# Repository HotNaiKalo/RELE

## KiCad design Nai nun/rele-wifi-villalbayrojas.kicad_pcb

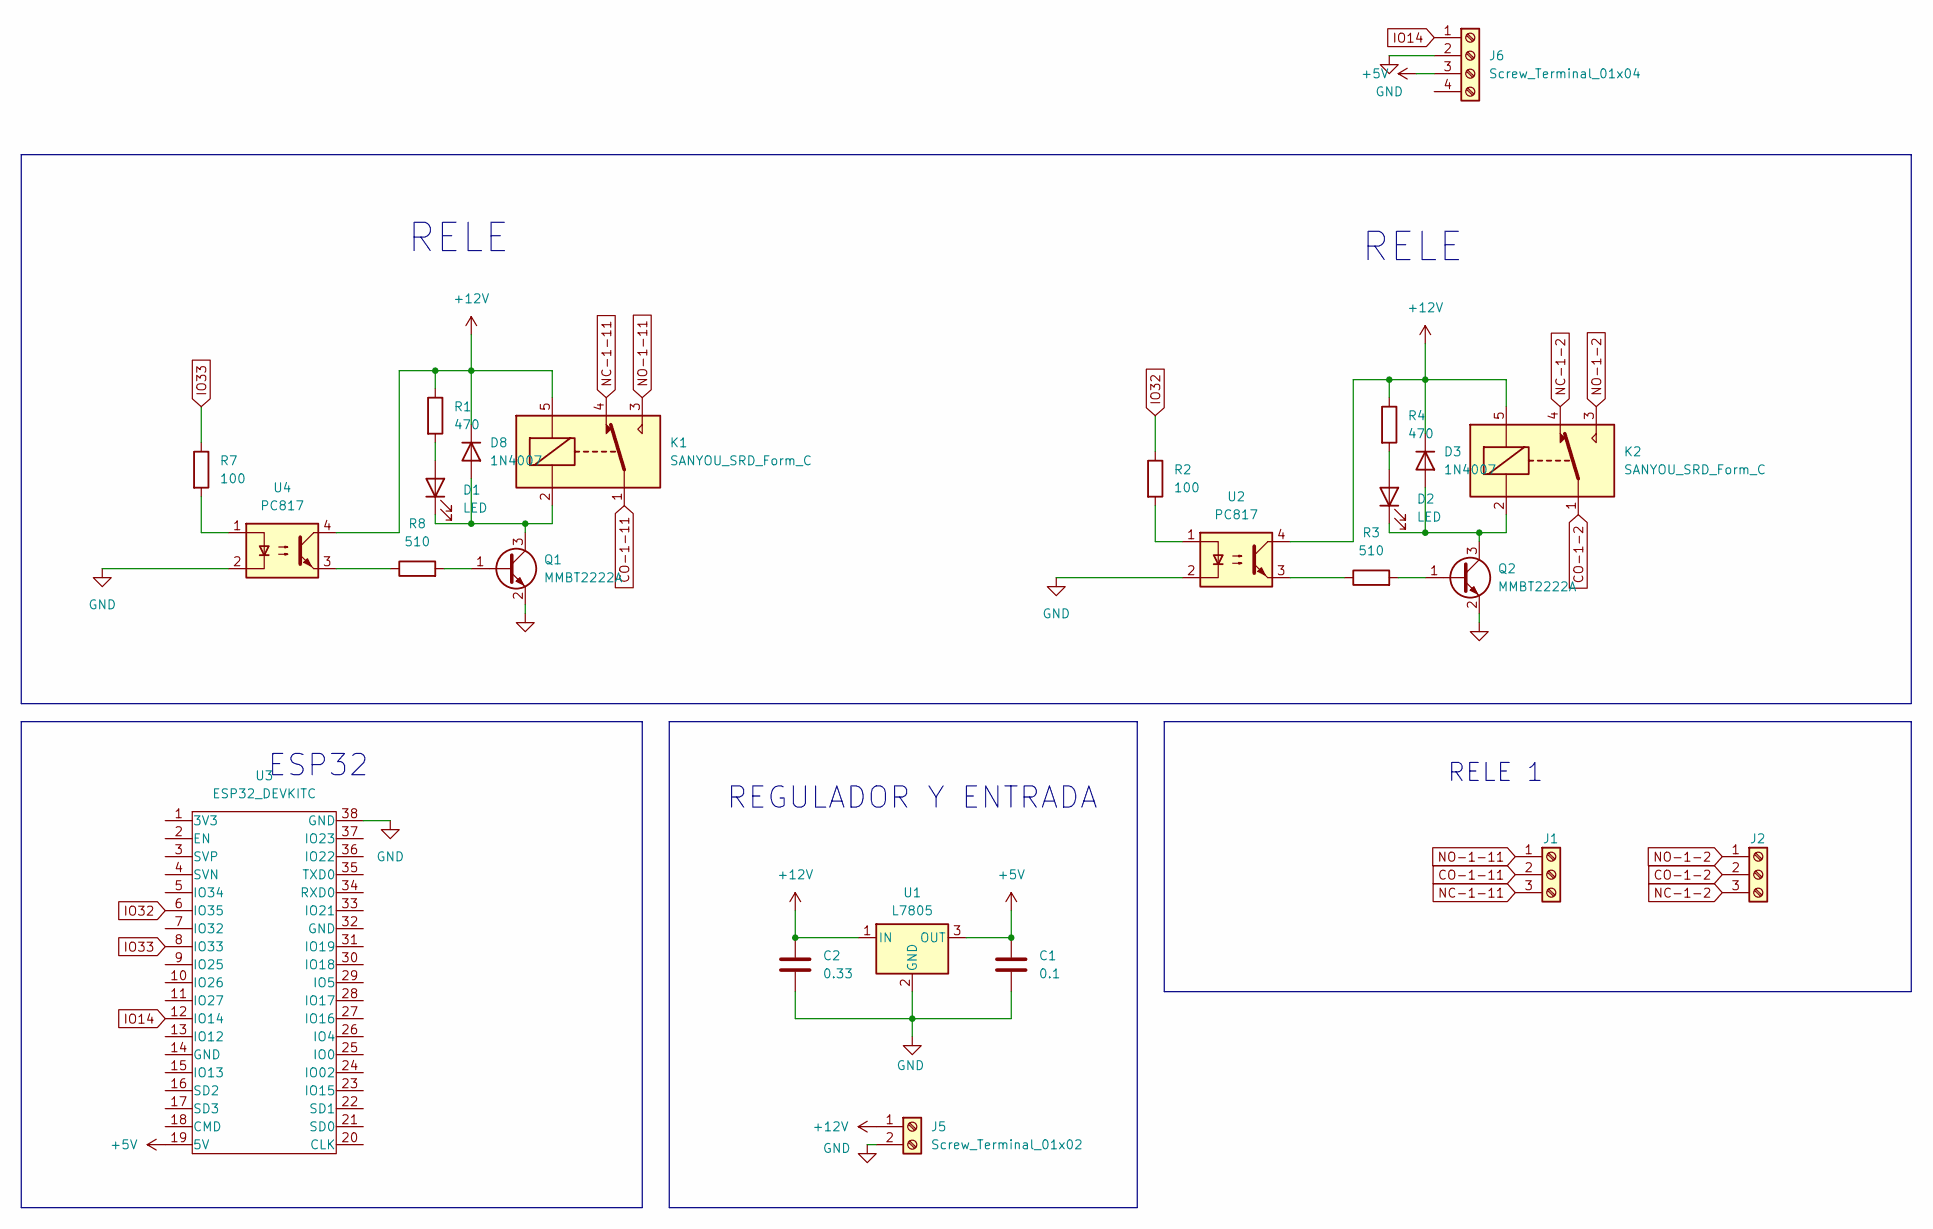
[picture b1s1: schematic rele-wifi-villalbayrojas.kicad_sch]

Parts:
C1: 0.1; C_0805_2012Metric
C2: 0.33; C_0805_2012Metric
D1, D2: LED; LED_0805_2012Metric
D3, D8: 1N4007; D_DO-41_SOD81_P10.16mm_Horizontal
J1, J2: Relay1; TerminalBlock_MaiXu_MX126-5.0-03P_1x03_P5.00mm
J5: Screw_Terminal_01x02; TerminalBlock_MaiXu_MX126-5.0-02P_1x02_P5.00mm
J6: Screw_Terminal_01x04; TerminalBlock_MaiXu_MX126-5.0-04P_1x04_P5.00mm
K1, K2: SANYOU_SRD_Form_C; Relay_SPDT_SANYOU_SRD_Series_Form_C
Q1, Q2: MMBT2222A; SOT-23
R1, R4: 470; R_0805_2012Metric
R2, R7: 100; R_0805_2012Metric
R3, R8: 510; R_0805_2012Metric
U1: L7805; TO-220-3_Vertical
U2, U4: PC817; DIP-4_W7.62mm
U3: ESP32_DEVKITC

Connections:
+5V: C1.1, J6.3, U1.3 (OUT), U3.19 (5V)
+12V: C2.1, D3.1 (K), D8.1 (K), J5.1, K1.5, K2.5, R1.1, R4.1, U1.1 (IN), U2.4, U4.4
CO-1-2: J2.2, K2.1
CO-1-11: J1.2, K1.1
GND: C1.2, C2.2, J5.2, J6.2, Q1.2 (E), Q2.2 (E), U1.2 (GND), U2.2, U3.38 (GND), U4.2
IO14: J6.1, U3.12 (IO14)
IO32: R2.1, U3.6 (IO35)
IO33: R7.1, U3.8 (IO33)
NC-1-2: J2.3, K2.4
NC-1-11: J1.3, K1.4
NO-1-2: J2.1, K2.3
NO-1-11: J1.1, K1.3
unnamed: D1.2 (A), R1.2
unnamed: D1.1 (K), D8.2 (A), K1.2, Q1.3 (C)
unnamed: D2.2 (A), R4.2
unnamed: D2.1 (K), D3.2 (A), K2.2, Q2.3 (C)
unnamed: Q1.1 (B), R8.2
unnamed: Q2.1 (B), R3.2
unnamed: R2.2, U2.1
unnamed: R3.1, U2.3
unnamed: R7.2, U4.1
unnamed: R8.1, U4.3

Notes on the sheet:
RELE
ESP32
RELE 1
REGULADOR Y ENTRADA

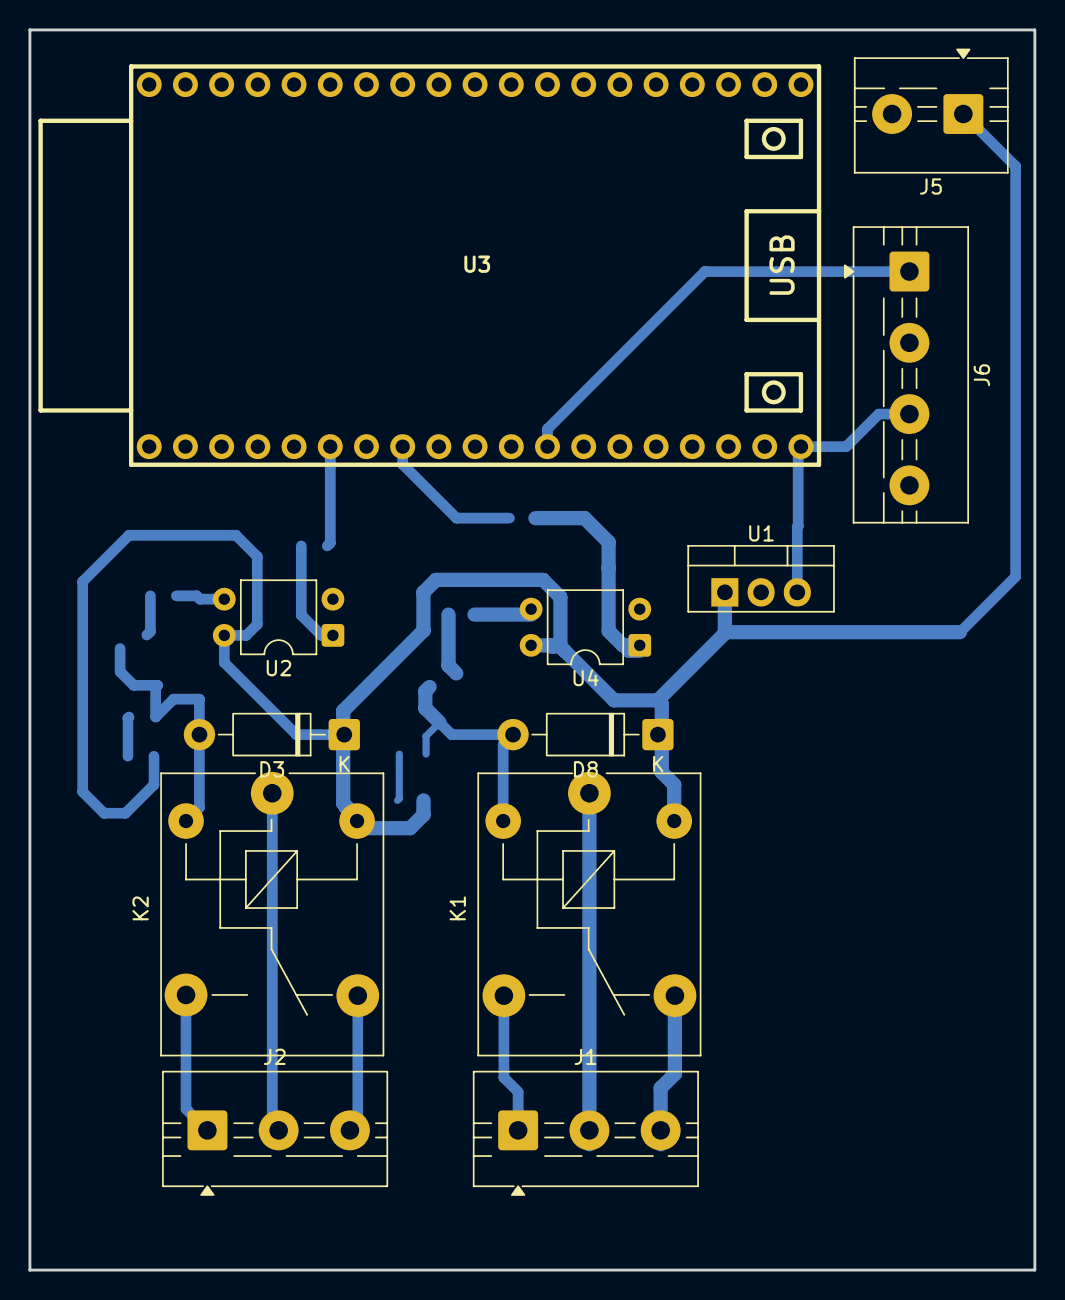
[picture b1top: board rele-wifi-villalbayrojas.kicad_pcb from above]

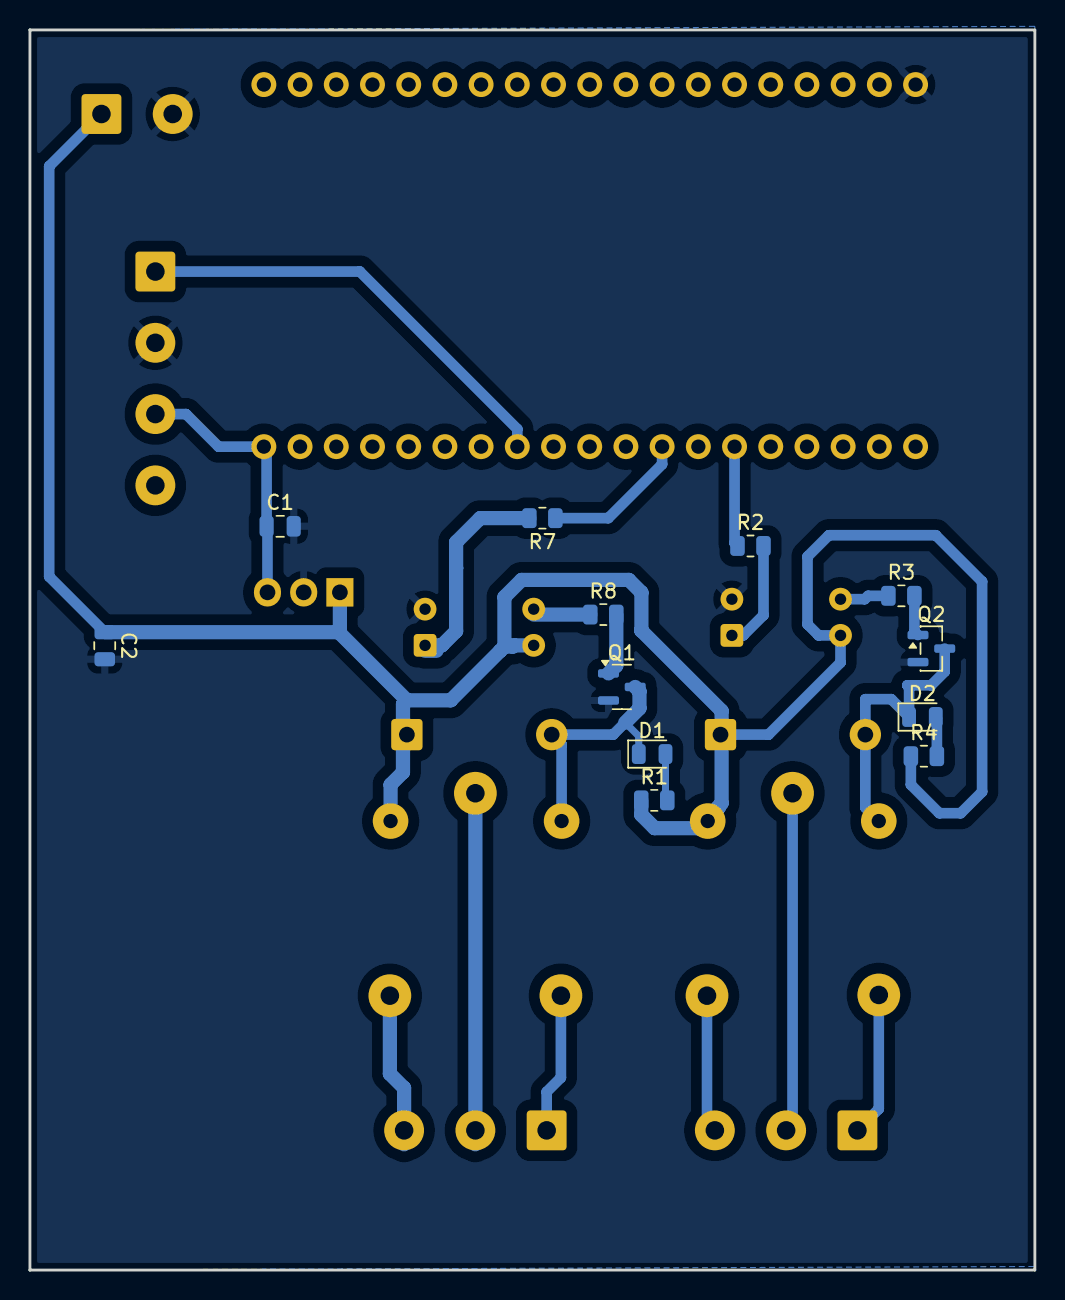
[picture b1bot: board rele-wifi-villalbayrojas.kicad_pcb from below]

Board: 2 copper layers, 70.5 x 87.0 mm, 24 parts (12 on the bottom side), 22 nets.

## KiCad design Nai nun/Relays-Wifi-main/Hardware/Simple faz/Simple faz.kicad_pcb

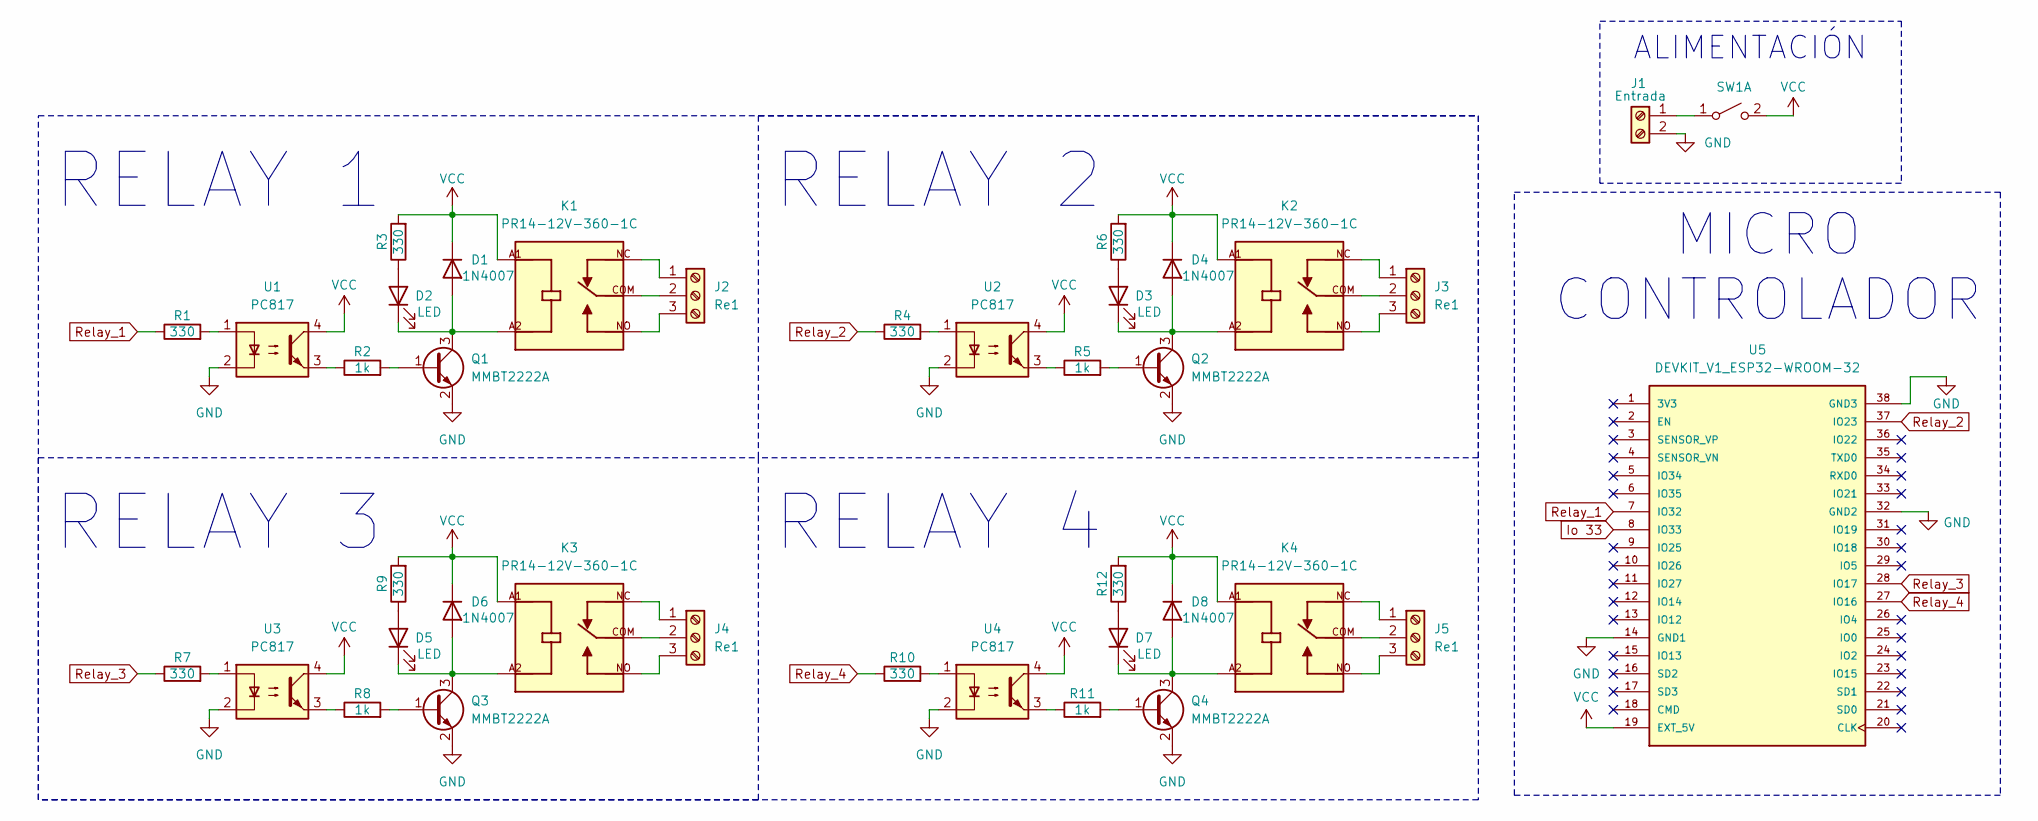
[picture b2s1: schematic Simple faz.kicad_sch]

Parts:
D1, D4, D6, D8: 1N4007; D_SMA
D2, D3, D5, D7: LED; LED_0805_2012Metric
J1: Entrada; TerminalBlock_4Ucon_1x02_P3.50mm_Vertical
J2, J3, J4, J5: Re1; TerminalBlock_4Ucon_1x03_P3.50mm_Vertical
K1, K2, K3, K4: PR14-12V-360-1C; RELAY_PR14-12V-360-1C; PARTREV 1.0
Q1, Q2, Q3, Q4: MMBT2222A; SOT-23
R1, R3, R4, R6, R7, R9, R10, R12: 330; R_0805_2012Metric_Pad1.20x1.40mm_HandSolder
R2, R5, R8, R11: 1k; R_0805_2012Metric_Pad1.20x1.40mm_HandSolder
SW1: PinSocket_1x02_P2.54mm_Vertical
U1, U2, U3, U4: PC817; SMDIP-4_W7.62mm
U5: DEVKIT_V1_ESP32-WROOM-32; ESP32S; PARTREV N/A

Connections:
GND: J1.2, Q1.2 (E), Q2.2 (E), Q3.2 (E), Q4.2 (E), U1.2, U2.2, U3.2, U4.2, U5.14 (GND1), U5.32 (GND2), U5.38 (GND3)
Io 33: U5.8 (IO33)
unnamed: D1.2 (A), D2.1 (K), K1.A2, Q1.3 (C)
unnamed: D2.2 (A), R3.1
unnamed: D3.2 (A), R6.1
unnamed: D3.1 (K), D4.2 (A), K2.A2, Q2.3 (C)
unnamed: D5.2 (A), R9.1
unnamed: D5.1 (K), D6.2 (A), K3.A2, Q3.3 (C)
unnamed: D7.2 (A), R12.1
unnamed: D7.1 (K), D8.2 (A), K4.A2, Q4.3 (C)
unnamed: J1.1, SW1.1 (A)
unnamed: J2.1, K1.NC
unnamed: J2.2, K1.COM
unnamed: J2.3, K1.NO
unnamed: J3.1, K2.NC
unnamed: J3.2, K2.COM
unnamed: J3.3, K2.NO
unnamed: J4.1, K3.NC
unnamed: J4.2, K3.COM
unnamed: J4.3, K3.NO
unnamed: J5.1, K4.NC
unnamed: J5.2, K4.COM
unnamed: J5.3, K4.NO
unnamed: Q1.1 (B), R2.2
unnamed: Q2.1 (B), R5.2
unnamed: Q3.1 (B), R8.2
unnamed: Q4.1 (B), R11.2
unnamed: R1.2, U1.1
unnamed: R2.1, U1.3
unnamed: R4.2, U2.1
unnamed: R5.1, U2.3
unnamed: R7.2, U3.1
unnamed: R8.1, U3.3
unnamed: R10.2, U4.1
unnamed: R11.1, U4.3
Relay_1: R1.1, U5.7 (IO32)
Relay_2: R4.1, U5.37 (IO23)
Relay_3: R7.1, U5.28 (IO17)
Relay_4: R10.1, U5.27 (IO16)
VCC: D1.1 (K), D4.1 (K), D6.1 (K), D8.1 (K), K1.A1, K2.A1, K3.A1, K4.A1, R3.2, R6.2, R9.2, R12.2, SW1.2 (B), U1.4, U2.4, U3.4, U4.4, U5.19 (EXT_5V)

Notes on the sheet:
ALIMENTACIÓN
RELAY 4
RELAY 3
MICRO CONTROLADOR
RELAY 2
RELAY 1

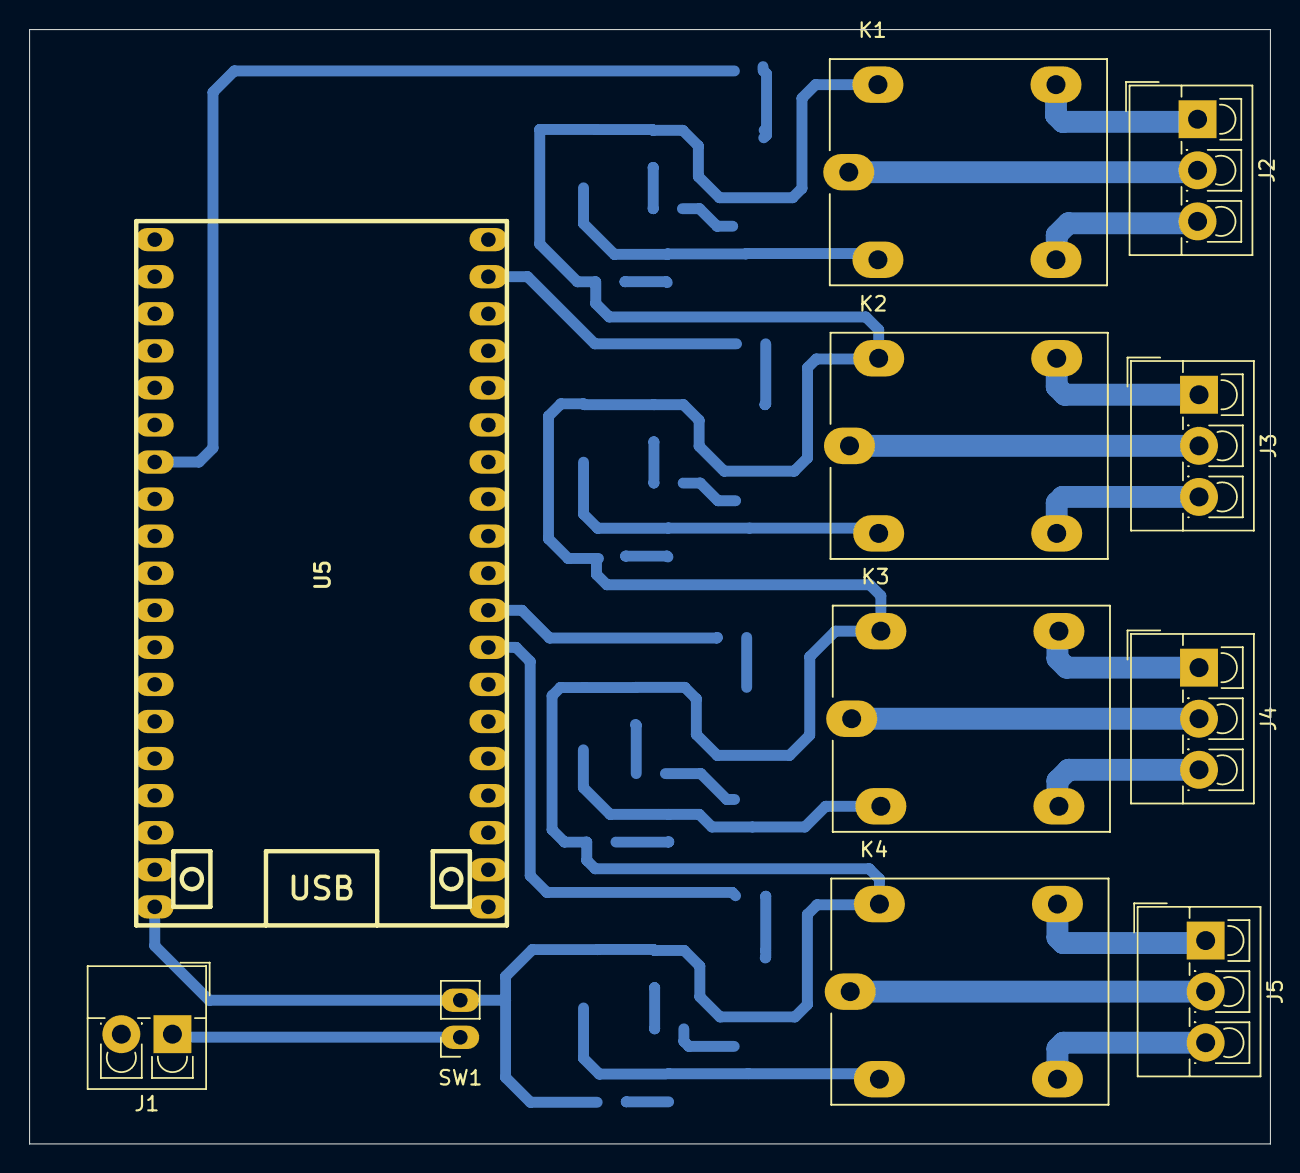
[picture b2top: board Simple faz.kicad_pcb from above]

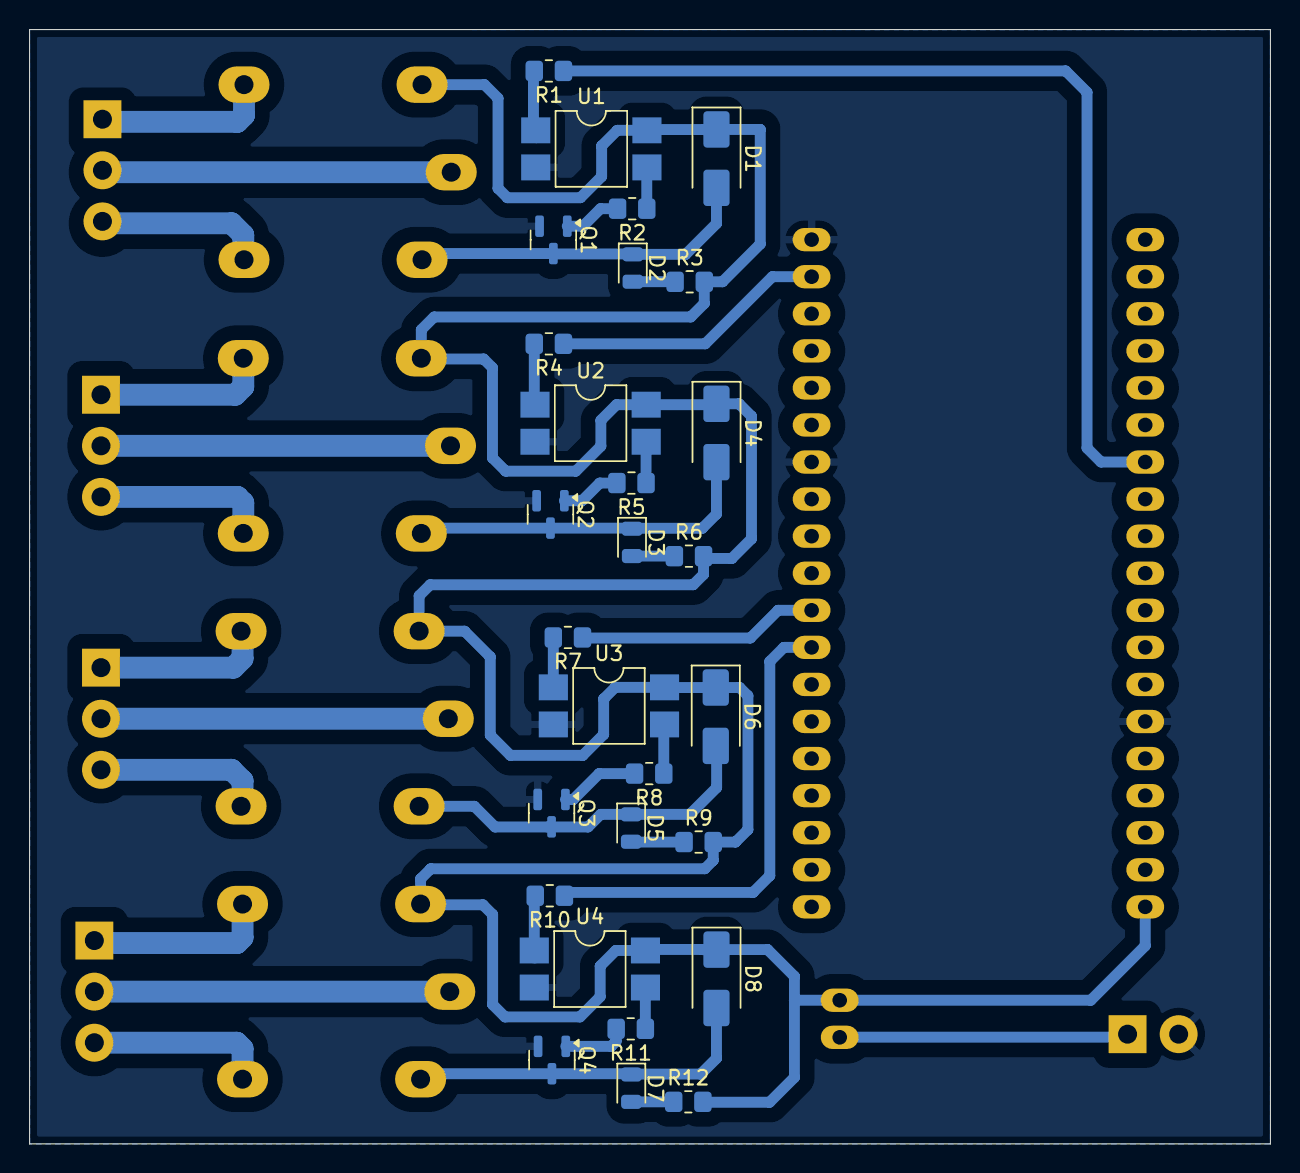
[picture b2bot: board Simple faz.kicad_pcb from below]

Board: 2 copper layers, 85.0 x 76.4 mm, 39 parts (28 on the bottom side), 39 nets.
